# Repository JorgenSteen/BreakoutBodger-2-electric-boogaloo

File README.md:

This is the breakout bodger 2 electric boogaloo, which is a continuation on breakout bodger deluxe.
It is a basic breakout board for atmel controller atmega328, but can also work for chips with similar pinouts.

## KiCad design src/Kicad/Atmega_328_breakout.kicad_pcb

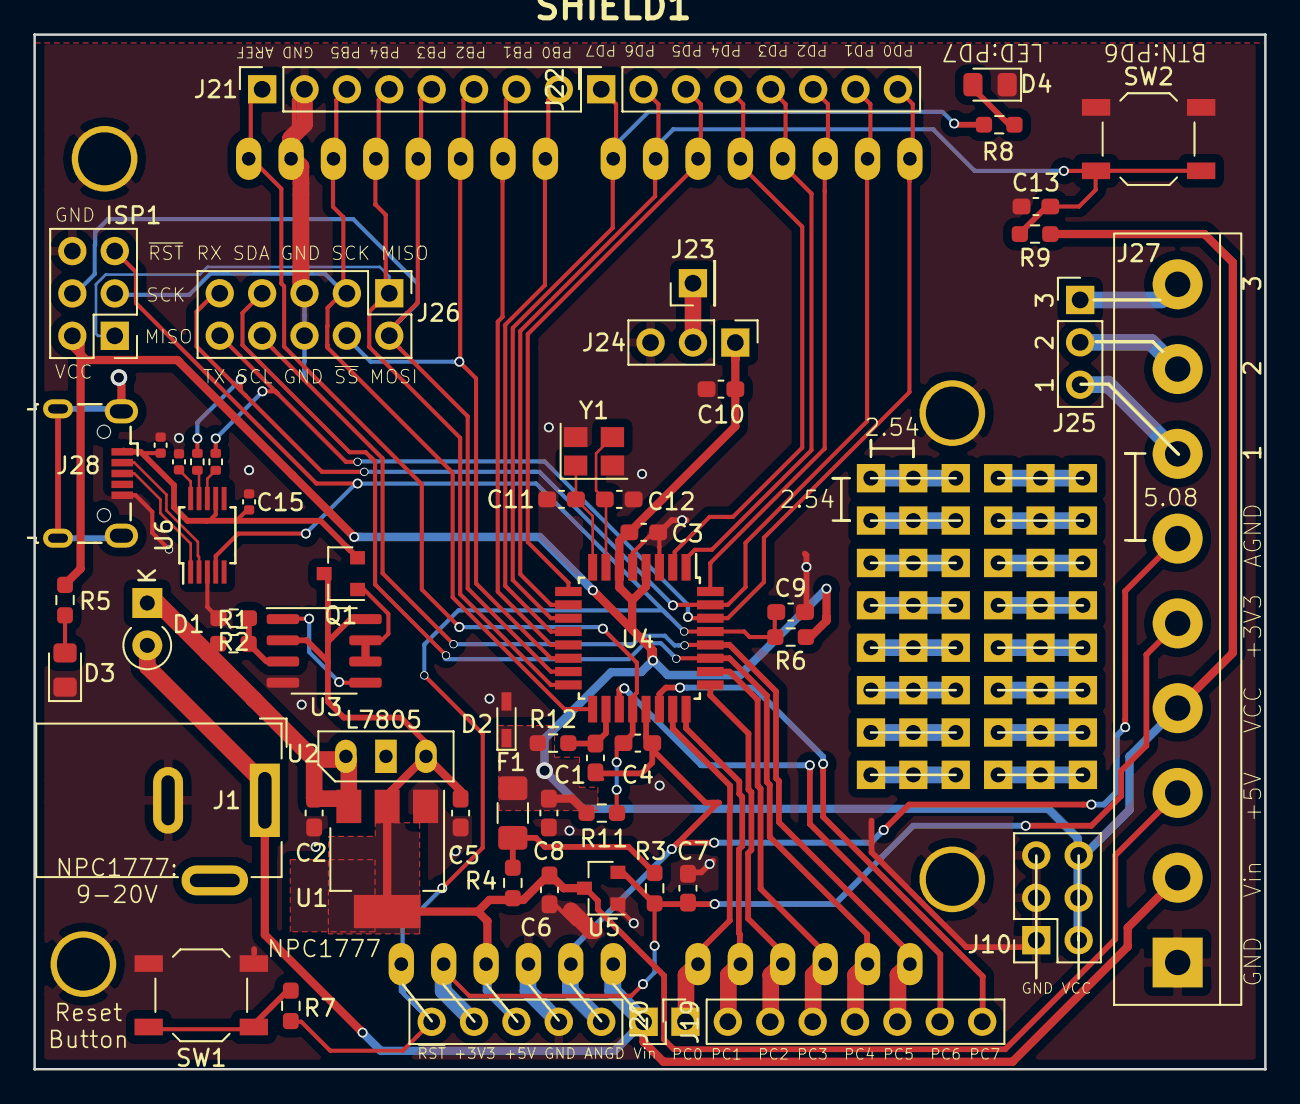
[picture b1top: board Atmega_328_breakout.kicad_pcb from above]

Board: 2 copper layers, 73.8 x 62.0 mm, 75 parts (1 on the bottom side), 67 nets.

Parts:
C1, C3, C4, C5, C7, C8, C9, C13: 100n; C_0603_1608Metric_Pad1.08x0.95mm_HandSolder
C2, C6, C10: 1u; C_0603_1608Metric_Pad1.08x0.95mm_HandSolder
C11, C12: 22p; C_0603_1608Metric_Pad1.08x0.95mm_HandSolder
C14, C15, C16: 100n; C_0402_1005Metric
D1: D_Schottky; D_A-405_P2.54mm_Vertical_KathodeUp
D2: 5,5+ Zener; D_SC-80_HandSoldering
D3: LED on; LED_0805_2012Metric_Pad1.15x1.40mm_HandSolder
D4: LED user; LED_0805_2012Metric_Pad1.15x1.40mm_HandSolder
F1: Polyfuse; Fuse_1206_3216Metric_Pad1.42x1.75mm_HandSolder
ISP1: AVR-ISP-6; PinHeader_2x03_P2.54mm_Vertical
J1: Jack-DC; BarrelJack_Wuerth_6941xx301002
J2, J3, J4, J5, J6, J7, J8, J9, J11, J12, J13, J14, J15, J16, J17, J18: 01x03; conn_01x03_square
J10: Conn_01x06; PinSocket_2x03_P2.54mm_Vertical
J19: Power_connector; PinSocket_1x06_P2.54mm_Vertical
J20: ADC_Connector; PinSocket_1x08_P2.54mm_Vertical
J21: PORB++_connector; PinSocket_1x08_P2.54mm_Vertical
J22: PORD_connector; PinSocket_1x08_P2.54mm_Vertical
J23: Conn_01x01; PinHeader_1x01_P2.54mm_Vertical
J24: Device_Connector; PinHeader_1x03_P2.54mm_Vertical
J25: Pin out; PinHeader_1x03_P2.54mm_Vertical
J26: Com_header; PinHeader_2x05_P2.54mm_Vertical
J27: Power terminal; TerminalBlock_bornier-9_P5.08mm
J28: USB; USB_Micro-B_Wuerth_629105150521
LOGO1: Logo_Open_Hardware_Large; BB2QR
Q1: AO3401A; SOT-23
R1, R2: 10k; R_0603_1608Metric_Pad0.98x0.95mm_HandSolder
R3: 0.0R; R_0603_1608Metric_Pad0.98x0.95mm_HandSolder
R4, R11, R12: 0R; R_0603_1608Metric_Pad0.98x0.95mm_HandSolder
R5, R8: 1k; R_0603_1608Metric_Pad0.98x0.95mm_HandSolder
R6: 4,7k; R_0603_1608Metric_Pad0.98x0.95mm_HandSolder
R7: 330; R_0603_1608Metric_Pad0.98x0.95mm_HandSolder
R9: 100kR; R_0603_1608Metric_Pad0.98x0.95mm_HandSolder
R10, R13: 200; R_0402_1005Metric
SHIELD1: ATMEL_SHIELD; AtmelSHIELD
SW1, SW2: SW_Push; SW_SPST_TL3342
U1: NCP1117-5; SOT-223-3_TabPin2
U2: L7805; TO-220-ver2
U3: LM358; SOIC-8_3.9x4.9mm_P1.27mm
U4: ATMEGA328P-AU; TQFP-32_7x7mm_P0.8mm
U5: MCP1700-33; SOT-23
U6: CH340E; MSOP-10_3x3mm_P0.5mm
Y1: Crystal_GND24; Crystal_SMD_3225-4Pin_3.2x2.5mm

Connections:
+3V3: C7.2, J19.5, J27.5, R3.1, SHIELD1.3V3, U5.2
+5V: C5.2, C6.2, J19.4, J27.3, Q1.3, R4.1, SHIELD1.5V, U1.2, U2.3, U3.2, U3.8, U5.3
ADC6: J20.7, U4.19
ADC7: J20.8, U4.22
AGND: C1.1, C4.1, J19.2, J27.6, SHIELD1.GND2, U4.21
AREF: C4.2, J21.1, R11.2, SHIELD1.AREF, U4.20
AVCC: C1.2, R12.2, U4.18
GND: C2.1, C3.1, C5.1, C6.1, C7.1, C8.2, C9.2, C10.1, C11.1, C12.1, C13.1, C14.1, C15.1, C16.1, D2.2, D3.1, D4.1, ISP1.6, J1.2, J10.1, J10.3, J10.5, J19.3, J21.2, J24.3, J26.5, J26.6, J27.1, J28.5, R2.2, SHIELD1.GND1, SHIELD1.GND3, SHIELD1.GNDS, SW1.2, SW2.1, U1.1, U2.2, U3.4, U4.3, U4.5, U5.1, U6.3, Y1.2, Y1.4
unnamed: C2.2, D1.1, R1.1, U1.3, U2.1
unnamed: C16.2, U6.10
unnamed: D3.2, R5.2
unnamed: D4.2, R8.2
unnamed: F1.1, R3.2, R4.2
unnamed: J2.1, J2.2, J2.3
unnamed: J3.1, J3.2, J3.3
unnamed: J4.1, J4.2, J4.3
unnamed: J5.1, J5.2, J5.3
unnamed: J6.1, J6.2, J6.3
unnamed: J7.1, J7.2, J7.3
unnamed: J8.1, J8.2, J8.3
unnamed: J9.1, J9.2, J9.3
unnamed: J11.1, J11.2, J11.3
unnamed: J12.1, J12.2, J12.3
unnamed: J13.1, J13.2, J13.3
unnamed: J14.1, J14.2, J14.3
unnamed: J15.1, J15.2, J15.3
unnamed: J16.1, J16.2, J16.3
unnamed: J17.1, J17.2, J17.3
unnamed: J18.1, J18.2, J18.3
unnamed: J23.1, J24.2
unnamed: J25.1, J27.9
unnamed: J25.2, J27.8
unnamed: J25.3, J27.7
unnamed: J28.2, U6.2
unnamed: J28.3, U6.1
unnamed: Q1.1, U3.6, U3.7
unnamed: R1.2, R2.1, U3.3
unnamed: R7.1, SW1.1
unnamed: R10.1, U6.8
unnamed: R13.1, U6.9
unnamed: U3.1, U3.5
PB0: J21.8, SHIELD1.8, U4.12
PB1: J21.7, SHIELD1.9, U4.13
PB2: J21.6, J26.4, SHIELD1.10, U4.14
PB3: ISP1.4, J21.5, J26.2, SHIELD1.11, U4.15
PB4: ISP1.1, J21.4, J26.1, SHIELD1.12, U4.16
PB5: ISP1.3, J21.3, J26.3, SHIELD1.13, U4.17
PC0: J20.1, SHIELD1.AD0, U4.23
PC1: J20.2, SHIELD1.AD1, U4.24
PC2: J20.3, SHIELD1.AD2, U4.25
PC3: J20.4, SHIELD1.AD3, U4.26
PC4(SDA): J20.5, J26.7, SHIELD1.AD4, U4.27
PC5(SCL): J20.6, J26.8, SHIELD1.AD5, U4.28
PD0(RX): J22.8, J26.10, R10.2, SHIELD1.0, U4.30
PD1(TX): J22.7, J26.9, R13.2, SHIELD1.1, U4.31
PD2: J22.6, SHIELD1.2, U4.32
PD3: J22.5, SHIELD1.3, U4.1
PD4: J22.4, SHIELD1.4, U4.2
PD5: J22.3, SHIELD1.5, U4.9
PD6: C13.2, J22.2, R9.2, SHIELD1.6, SW2.2, U4.10
PD7: J22.1, R8.1, SHIELD1.7, U4.11
VCC: C3.2, C8.1, C10.2, D2.1, F1.2, ISP1.2, J10.2, J10.4, J10.6, J24.1, J27.4, R5.1, R6.1, R9.1, R11.1, R12.1, U4.4, U4.6
VUSB: C14.2, C15.2, J28.1, Q1.2, U6.7
V_supply: D1.2, J1.1, J19.1, J27.2, SHIELD1.V_IN
XTAL1(PB6): C12.2, U4.7, Y1.3
XTAL2(PB7): C11.2, U4.8, Y1.1
~RESET: C9.1, ISP1.5, J19.6, R6.2, R7.2, SHIELD1.RST, U4.29, U6.4

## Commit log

2020-10-14 intial push
2020-10-16 initial push
2020-10-16 cahnged path
2020-10-17 path change
2020-10-17 fixed it for kicad 5
2020-10-17 last commit before merge
2020-10-17 double checked files
2020-10-17 copied edited files
2020-10-17 added available parts from jlcpcb for bom
2020-10-17 compiled and packed gerber
2020-10-17 replace as much as possible with smd
2020-10-18 All parts added and part number
2020-10-18 before switching
2020-10-18 Every thing is placed and files are created.
2020-10-18 Release-2.0
2020-10-18 started adding new parts
2020-10-18 updated scheme
2020-10-18 sent for production
2020-10-19 added png - last with NCP2221
2020-10-20 replaced serial to usb chip and added safety.
2020-10-20 Clean up
2020-11-07 clean up and added test code and box
2020-11-07 added arduino code
2020-11-14 added fusion360 schemtic for box
